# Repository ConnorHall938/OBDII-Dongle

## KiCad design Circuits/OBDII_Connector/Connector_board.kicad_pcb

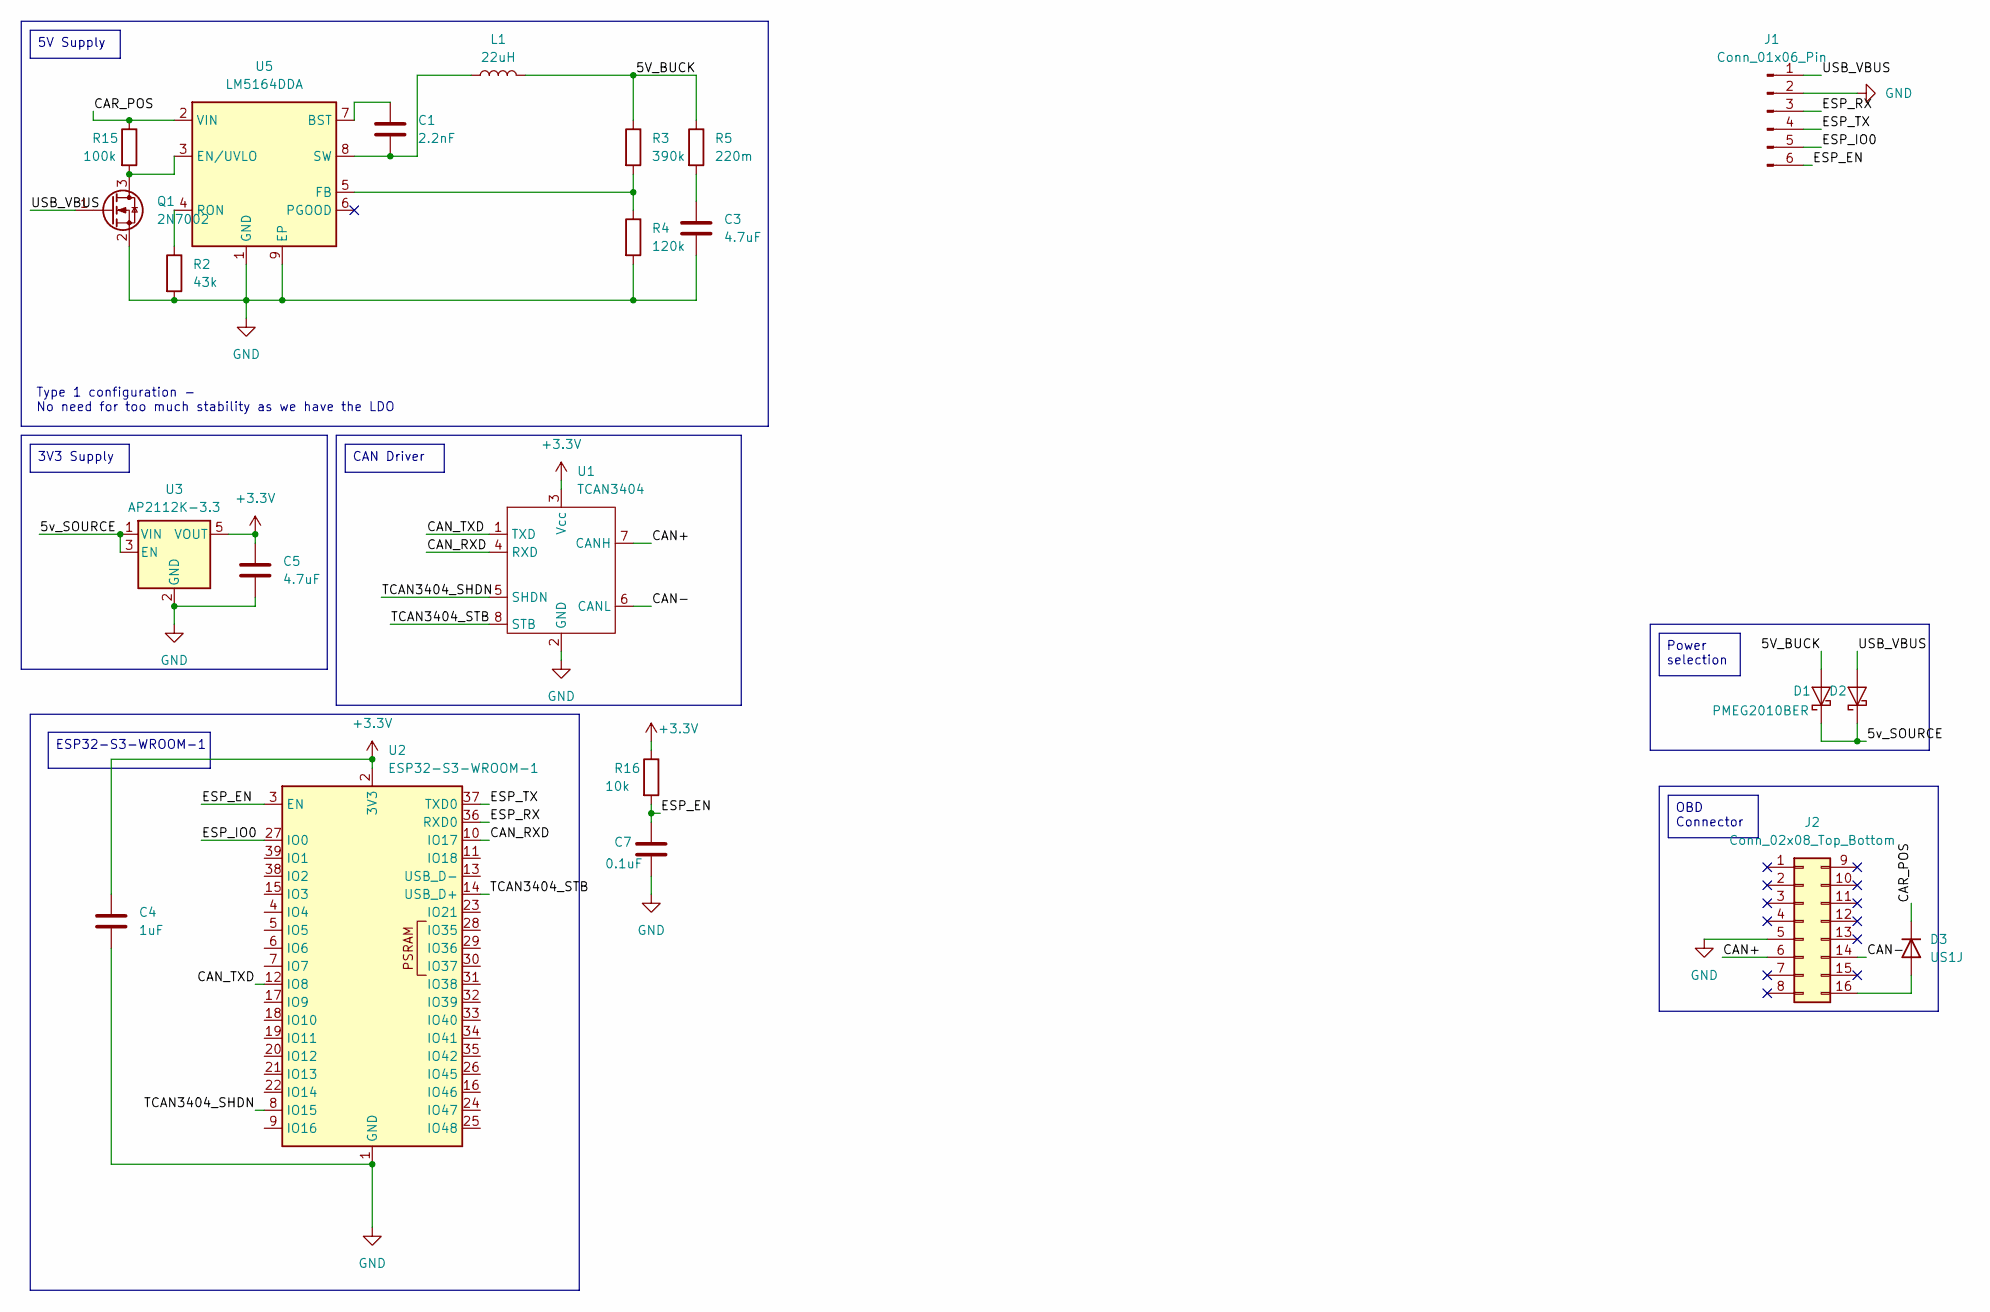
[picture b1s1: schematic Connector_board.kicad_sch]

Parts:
C1: 2.2nF; C_0805_2012Metric_Pad1.18x1.45mm_HandSolder
C3, C5: 4.7uF; C_0805_2012Metric_Pad1.18x1.45mm_HandSolder
C4: 1uF; C_0805_2012Metric_Pad1.18x1.45mm_HandSolder
C7: 0.1uF; C_0805_2012Metric_Pad1.18x1.45mm_HandSolder
D1, D2: PMEG2010BER; Nexperia_CFP3_SOD-123W
D3: US1J; D_SMA
J1: Conn_01x06_Pin; PinSocket_1x06_P2.54mm_Vertical
J2: Conn_02x08_Top_Bottom; PinSocket_2x08_P2.54mm_Vertical
L1: 22uH; L_Bourns_SRN6045TA
Q1: 2N7002; SOT-23
R2: 43k; R_0603_1608Metric_Pad0.98x0.95mm_HandSolder
R3: 390k; R_0603_1608Metric_Pad0.98x0.95mm_HandSolder
R4: 120k; R_0603_1608Metric_Pad0.98x0.95mm_HandSolder
R5: 220m; R_1206_3216Metric_Pad1.30x1.75mm_HandSolder
R15: 100k; R_0603_1608Metric_Pad0.98x0.95mm_HandSolder
R16: 10k; R_0603_1608Metric_Pad0.98x0.95mm_HandSolder
U1: TCAN3404; SOIC-8_3.9x4.9mm_P1.27mm
U2: ESP32-S3-WROOM-1
U3: AP2112K-3.3; SOT-23-5
U5: LM5164DDA; HSOP-8-1EP_3.9x4.9mm_P1.27mm_EP2.41x3.1mm_ThermalVias

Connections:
+3.3V: C4.1, C5.1, R16.1, U1.3 (Vcc), U2.2 (3V3), U3.5 (VOUT)
/5V_BUCK: D1.2 (A), L1.2, R3.1, R5.1
/5v_SOURCE: D1.1 (K), D2.1 (K), U3.1 (VIN), U3.3 (EN)
/CAN+: J2.6, U1.7 (CANH)
/CAN-: J2.14, U1.6 (CANL)
/CAN_RXD: U1.4 (RXD), U2.10 (IO17)
/CAN_TXD: U1.1 (TXD), U2.12 (IO8)
/CAR_POS: D3.1 (K), R15.1, U5.2 (VIN)
/ESP_EN: C7.1, J1.6, R16.2, U2.3 (EN)
/ESP_IO0: J1.5, U2.27 (IO0)
/ESP_RX: J1.3, U2.36 (RXD0)
/ESP_TX: J1.4, U2.37 (TXD0)
/TCAN3404_SHDN: U1.5 (SHDN), U2.8 (IO15)
/TCAN3404_STB: U1.8 (STB), U2.14 (USB_D+)
/USB_VBUS: D2.2 (A), J1.1, Q1.1 (G)
GND: C3.2, C4.2, C5.2, C7.2, J1.2, J2.5, Q1.2 (S), R2.2, R4.2, U1.2 (GND), U2.1 (GND), U2.40 (GND), U2.41 (GND), U3.2 (GND), U5.1 (GND), U5.9 (EP)
unnamed: C3.1, R5.2
unnamed: D3.2 (A), J2.16
unnamed: Q1.3 (D), R15.2, U5.3 (EN/UVLO)
unnamed: C1.1, U5.7 (BST)
unnamed: R3.2, R4.1, U5.5 (FB)
unnamed: R2.1, U5.4 (RON)
unnamed: C1.2, L1.1, U5.8 (SW)

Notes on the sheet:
Type 1 configuration - No need for too much stability as we have the LDO
5V Supply
3V3 Supply
CAN Driver
Power selection
OBD Connector
ESP32-S3-WROOM-1

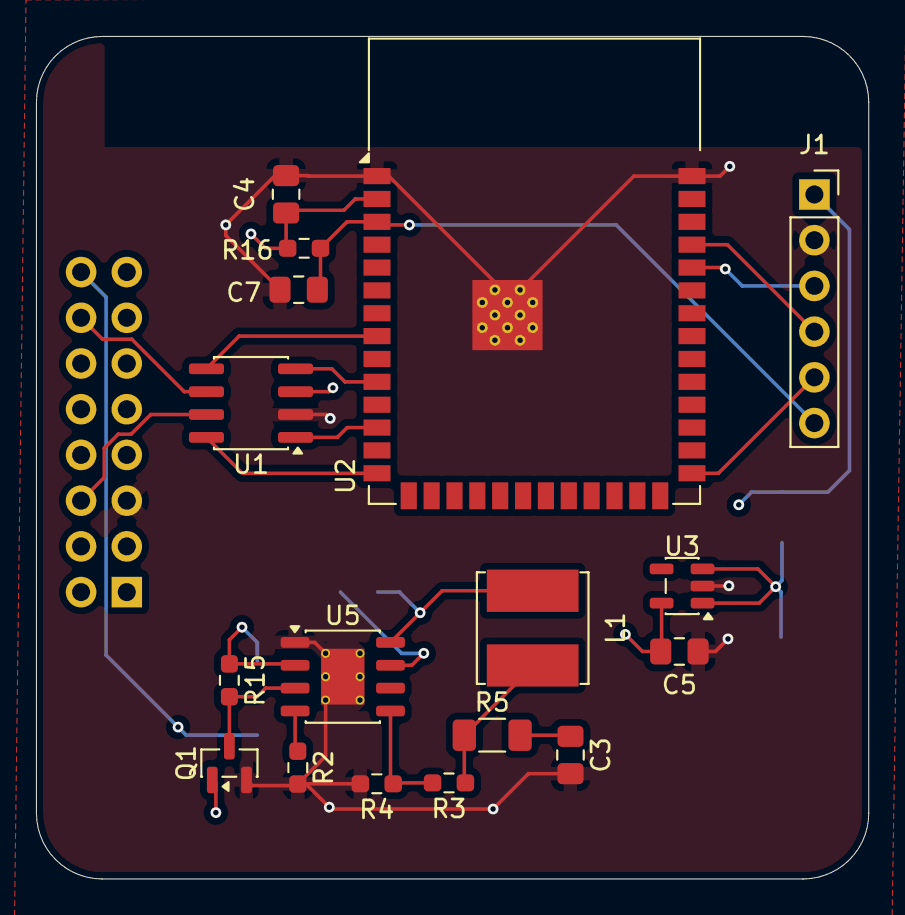
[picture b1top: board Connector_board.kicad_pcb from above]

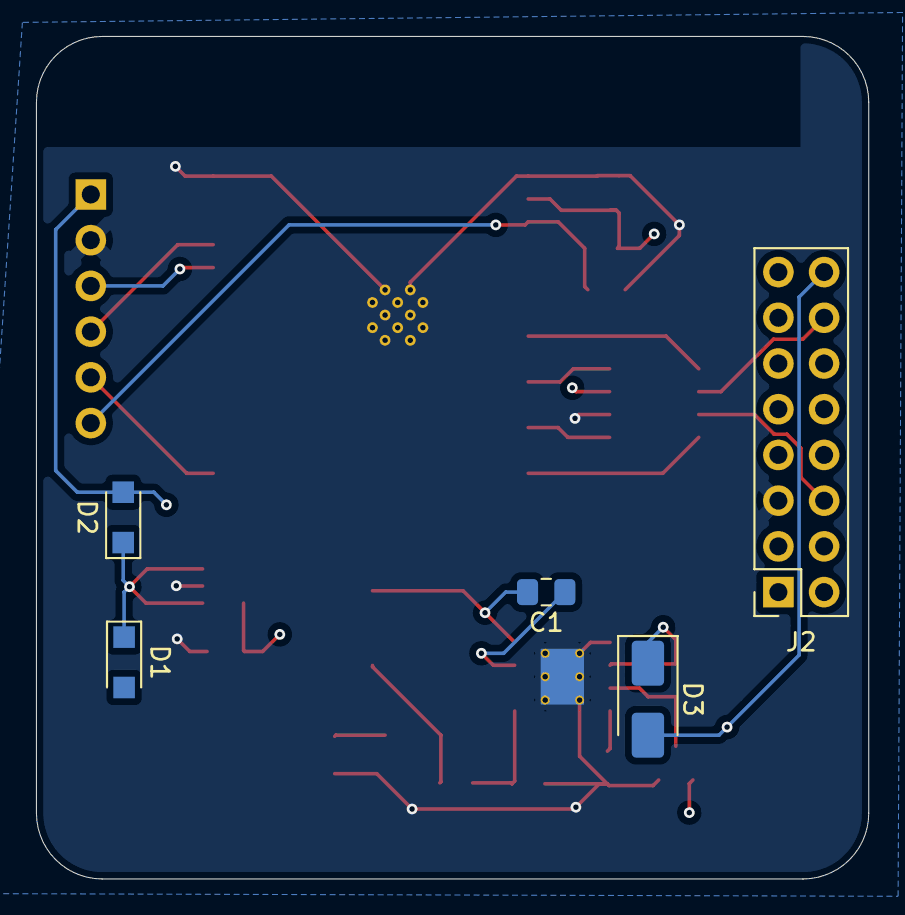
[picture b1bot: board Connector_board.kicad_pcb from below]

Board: 4 copper layers, 46.2 x 46.8 mm, 22 parts (5 on the bottom side), 23 nets.

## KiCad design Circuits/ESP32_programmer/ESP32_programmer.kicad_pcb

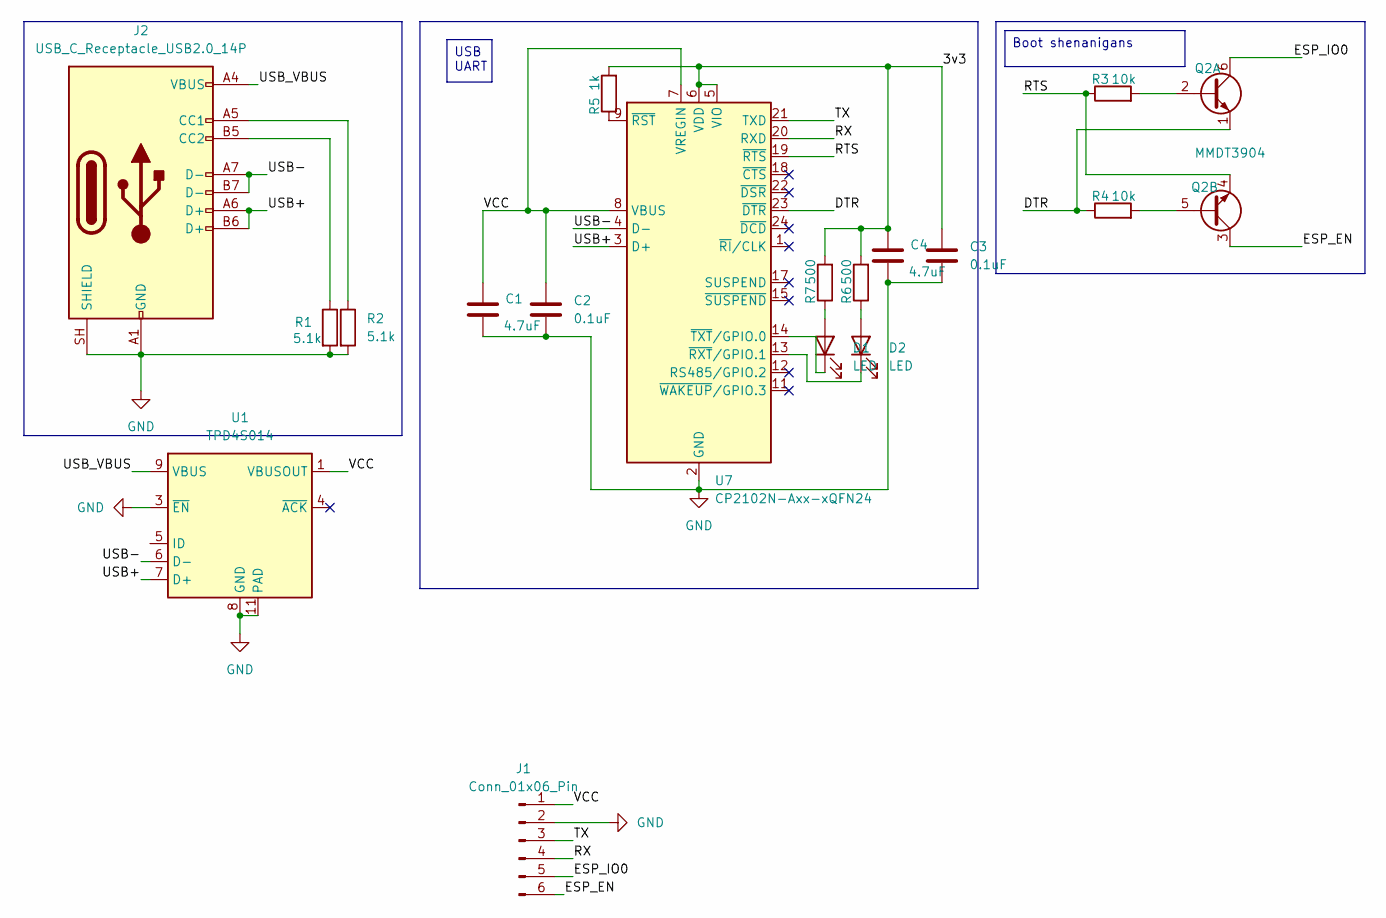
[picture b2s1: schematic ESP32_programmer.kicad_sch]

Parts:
C1, C4: 4.7uF; C_0805_2012Metric_Pad1.18x1.45mm_HandSolder
C2, C3: 0.1uF; C_0805_2012Metric_Pad1.18x1.45mm_HandSolder
D1, D2: LED; LED_1206_3216Metric_Pad1.42x1.75mm_HandSolder
J1: Conn_01x06_Pin; PinSocket_1x06_P2.54mm_Vertical
J2: USB_C_Receptacle_USB2.0_14P; USB_C_Receptacle_Amphenol_12401948E412A
Q2: MMDT3904; SOT-363_SC-70-6
R1, R2: 5.1k; R_0603_1608Metric_Pad0.98x0.95mm_HandSolder
R3, R4: 10k; R_0603_1608Metric_Pad0.98x0.95mm_HandSolder
R5: 1k; R_0603_1608Metric_Pad0.98x0.95mm_HandSolder
R6, R7: 500; R_0603_1608Metric_Pad0.98x0.95mm_HandSolder
U1: TPD4S014; Texas_S-PWSON-N10_ThermalVias
U7: CP2102N-Axx-xQFN24; QFN-24-1EP_4x4mm_P0.5mm_EP2.6x2.6mm

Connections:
/3v3: C3.1, C4.1, R5.2, R6.2, R7.2, U7.5 (VIO), U7.6 (VDD)
/DTR: Q2.1 (E1), R4.1, U7.23 (~DTR)
/ESP_EN: J1.6, Q2.3 (C2)
/ESP_IO0: J1.5, Q2.6 (C1)
/RTS: Q2.4 (E2), R3.1, U7.19 (~RTS)
/RX: J1.4, U7.20 (RXD)
/TX: J1.3, U7.21 (TXD)
/USB+: J2.A6 (D+), J2.B6 (D+), U1.7 (D+), U7.3 (D+)
/USB-: J2.A7 (D-), J2.B7 (D-), U1.6 (D-), U7.4 (D-)
/USB_VBUS: J2.A4 (VBUS), J2.A9 (VBUS), J2.B4 (VBUS), J2.B9 (VBUS), U1.9 (VBUS), U1.10 (VBUS)
/VCC: C1.1, C2.1, J1.1, U1.1 (VBUSOUT), U1.2 (VBUSOUT), U7.7 (VREGIN), U7.8 (VBUS)
GND: C1.2, C2.2, C3.2, C4.2, J1.2, J2.A1 (GND), J2.A12 (GND), J2.B1 (GND), J2.B12 (GND), J2.SH (SHIELD), R1.2, R2.2, U1.3 (~EN), U1.8 (GND), U1.11 (PAD), U7.2 (GND), U7.25 (GND)
unnamed: D1.2 (A), R7.1
unnamed: D1.1 (K), U7.14 (~TXT/GPIO.0)
unnamed: D2.2 (A), R6.1
unnamed: D2.1 (K), U7.13 (~RXT/GPIO.1)
unnamed: J2.A5 (CC1), R2.1
unnamed: J2.B5 (CC2), R1.1
unnamed: Q2.2 (B1), R3.2
unnamed: Q2.5 (B2), R4.2
unnamed: R5.1, U7.9 (~RST)

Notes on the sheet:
USB UART
Boot shenanigans

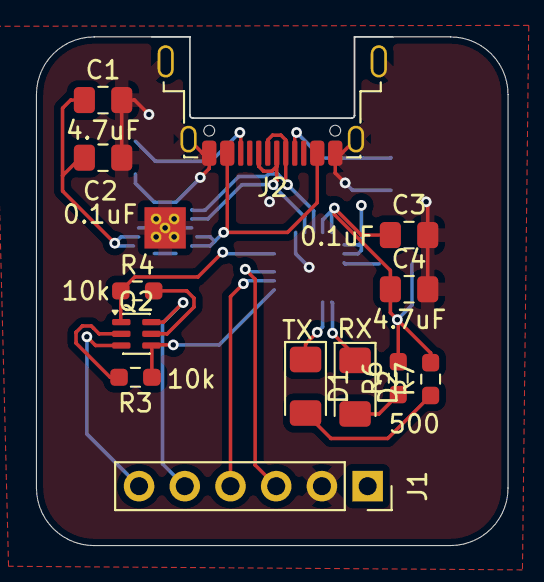
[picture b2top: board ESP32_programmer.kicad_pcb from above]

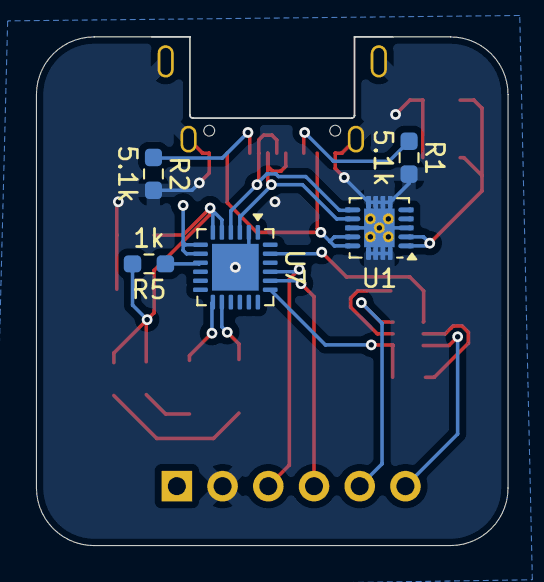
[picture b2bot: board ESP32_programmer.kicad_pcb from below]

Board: 4 copper layers, 26.2 x 28.3 mm, 18 parts (5 on the bottom side), 21 nets.

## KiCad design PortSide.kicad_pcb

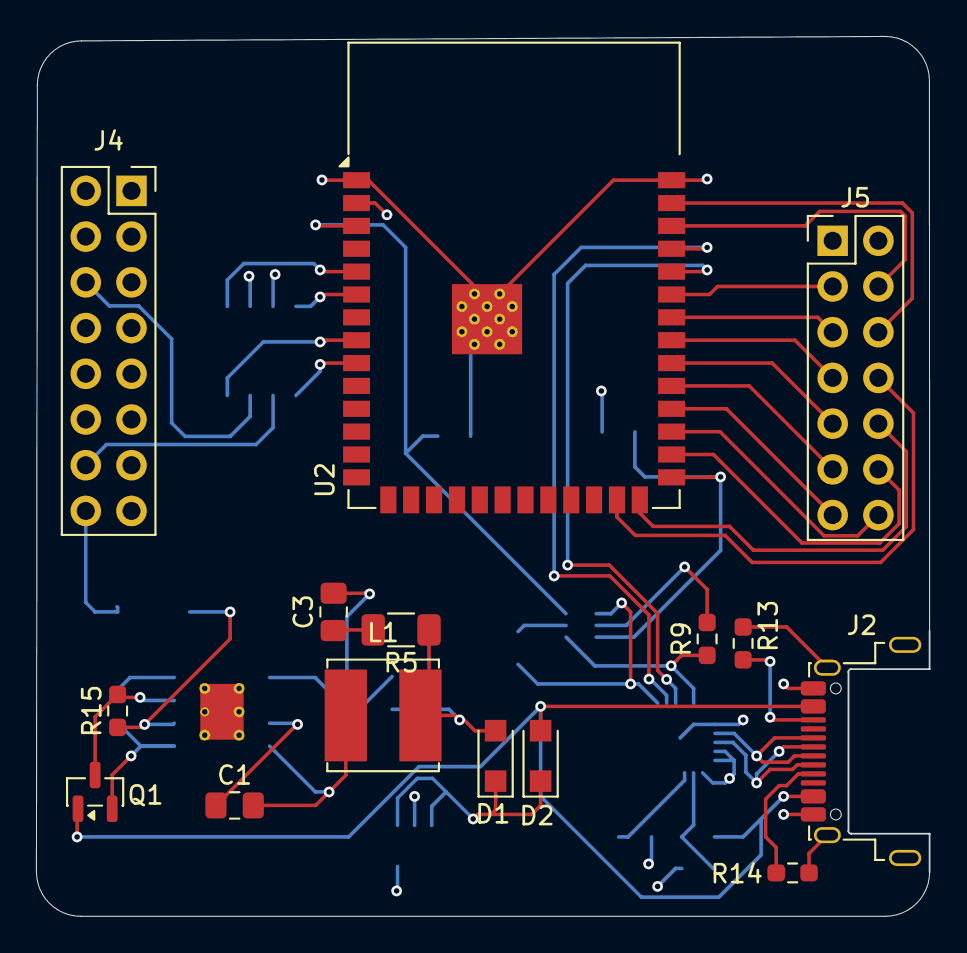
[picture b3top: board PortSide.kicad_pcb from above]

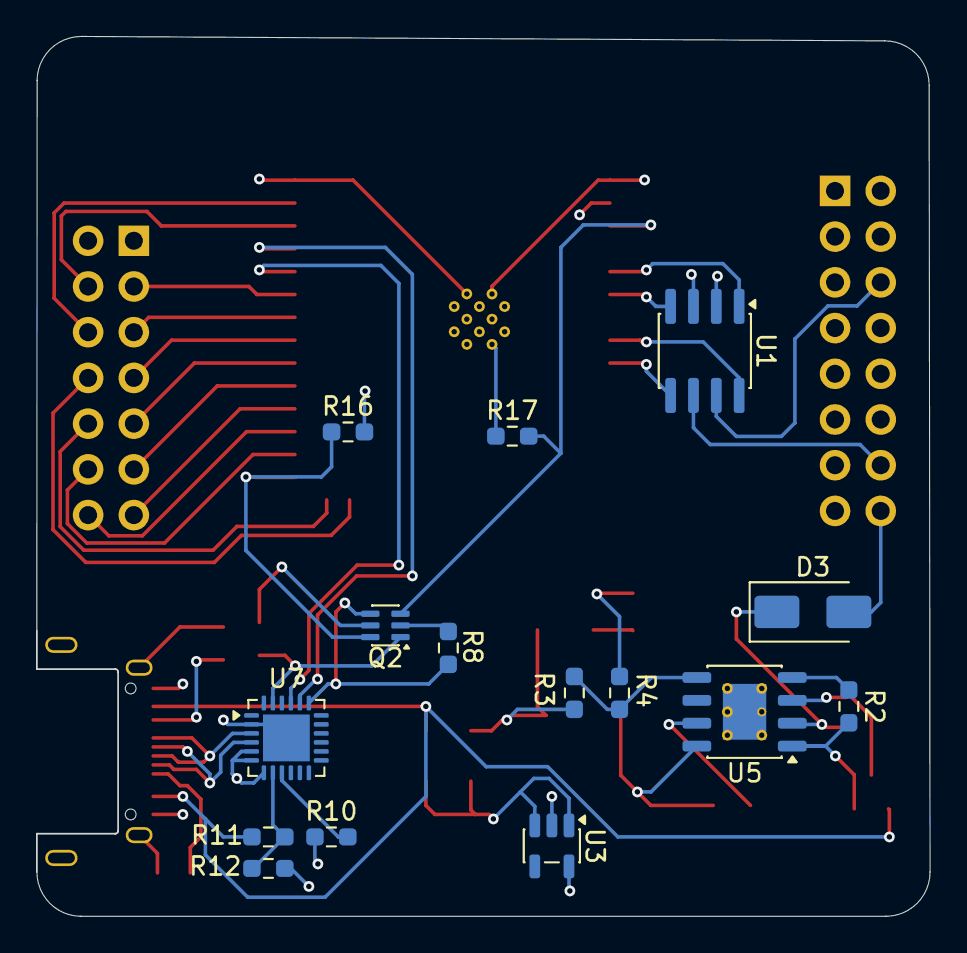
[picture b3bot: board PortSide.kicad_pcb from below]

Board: 4 copper layers, 49.6 x 48.9 mm, 30 parts (15 on the bottom side), 45 nets.

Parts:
C1: 2.2nF; C_0805_2012Metric_Pad1.18x1.45mm_HandSolder
C3: 4.7uF; C_0805_2012Metric_Pad1.18x1.45mm_HandSolder
D1, D2: PMEG2010BER; Nexperia_CFP3_SOD-123W
D3: US1J; D_SMA
J2: USB_C_Receptacle_USB2.0_14P; USB_C_Receptacle_Amphenol_12401948E412A
J4: Conn_02x08_Top_Bottom; PinSocket_2x08_P2.54mm_Vertical
J5: Conn_02x07_Counter_Clockwise; PinHeader_2x07_P2.54mm_Vertical
L1: 22uH; L_Bourns_SRN6045TA
Q1: 2N7002; SOT-23
Q2: MMDT3904; SOT-363_SC-70-6
R2: 43k; R_0603_1608Metric_Pad0.98x0.95mm_HandSolder
R3: 390k; R_0603_1608Metric_Pad0.98x0.95mm_HandSolder
R4: 120k; R_0603_1608Metric_Pad0.98x0.95mm_HandSolder
R5: 220m; R_1206_3216Metric_Pad1.30x1.75mm_HandSolder
R8, R9, R10: 1k; R_0603_1608Metric_Pad0.98x0.95mm_HandSolder
R11: 22k; R_0603_1608Metric_Pad0.98x0.95mm_HandSolder
R12: 47k; R_0603_1608Metric_Pad0.98x0.95mm_HandSolder
R13, R14: 5.1k; R_0603_1608Metric_Pad0.98x0.95mm_HandSolder
R15: 100k; R_0603_1608Metric_Pad0.98x0.95mm_HandSolder
R16, R17: 10k; R_0603_1608Metric_Pad0.98x0.95mm_HandSolder
U1: TCAN3404; SOIC-8_3.9x4.9mm_P1.27mm
U2: ESP32-S3-WROOM-1
U3: AP2112K-3.3; SOT-23-5
U5: LM5164DDA; HSOP-8-1EP_3.9x4.9mm_P1.27mm_EP2.41x3.1mm_ThermalVias
U7: CP2102N-Axx-xQFN24; QFN-24-1EP_4x4mm_P0.5mm_EP2.6x2.6mm

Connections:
+3.3V: J5.1, R10.1, U1.3 (Vcc), U2.2 (3V3), U3.5 (VOUT), U7.5 (VIO), U7.6 (VDD), U7.7 (VREGIN)
/5V_BUCK: D1.2 (A), L1.2, R3.1, R5.1
/5v_SOURCE: D1.1 (K), D2.1 (K), U3.1 (VIN), U3.3 (EN)
/CANH: J4.6, U1.7 (CANH)
/CANL: J4.14, U1.6 (CANL)
/CAN_RXD: U1.4 (RXD), U2.6 (IO6)
/CAN_TXD: U1.1 (TXD), U2.5 (IO5)
/CAR_POS: D3.1 (K), R15.1, U5.2 (VIN)
/DTR: Q2.1 (E1), R9.1, U7.23 (~DTR)
/ESP_EN: Q2.3 (C2), R17.2, U2.3 (EN)
/ESP_IO0: Q2.6 (C1), R16.1, U2.27 (IO0)
/ESP_RX: U2.36 (RXD0), U7.21 (TXD)
/ESP_TX: U2.37 (TXD0), U7.20 (RXD)
/LCD_CS: J5.3, U2.35 (IO42)
/LCD_DC: J5.5, U2.34 (IO41)
/LCD_LED: J5.8, U2.25 (IO48)
/LCD_MISO: J5.9, U2.32 (IO39)
/LCD_MOSI: J5.6, U2.39 (IO1)
/LCD_RESET: J5.4, U2.38 (IO2)
/LCD_SCK: J5.7, U2.33 (IO40)
/LCD_T_CLK: J5.10, U2.26 (IO45)
/LCD_T_CS: J5.11, U2.31 (IO38)
/LCD_T_DIN: J5.12, U2.28 (IO35)
/LCD_T_DO: J5.13, U2.30 (IO37)
/LCD_T_IRQ: J5.14, U2.29 (IO36)
/RTS: Q2.4 (E2), R8.1, U7.19 (~RTS)
/TCAN3404_SHDN: U1.5 (SHDN), U2.9 (IO16)
/TCAN3404_STB: U1.8 (STB), U2.8 (IO15)
/USB+: J2.A6 (D+), J2.B6 (D+), U7.3 (D+)
/USB-: J2.A7 (D-), J2.B7 (D-), U7.4 (D-)
/USB_VBUS: D2.2 (A), J2.A4 (VBUS), J2.A9 (VBUS), J2.B4 (VBUS), J2.B9 (VBUS), Q1.1 (G), R11.1
GND: C3.2, J2.A1 (GND), J2.A12 (GND), J2.B1 (GND), J2.B12 (GND), J2.SH (SHIELD), J4.5, J5.2, Q1.2 (S), R2.2, R4.2, R12.2, R13.2, R14.2, R16.2, R17.1, U1.2 (GND), U2.1 (GND), U2.40 (GND), U2.41 (GND), U3.2 (GND), U5.1 (GND), U5.9 (EP), U7.2 (GND), U7.25 (GND)
unnamed: C3.1, R5.2
unnamed: D3.2 (A), J4.16
unnamed: J2.A5 (CC1), R14.1
unnamed: J2.B5 (CC2), R13.1
unnamed: Q1.3 (D), R15.2, U5.3 (EN/UVLO)
unnamed: Q2.2 (B1), R8.2
unnamed: Q2.5 (B2), R9.2
unnamed: C1.1, U5.7 (BST)
unnamed: R3.2, R4.1, U5.5 (FB)
unnamed: R2.1, U5.4 (RON)
unnamed: C1.2, L1.1, U5.8 (SW)
unnamed: R11.2, R12.1, U7.8 (VBUS)
unnamed: R10.2, U7.9 (~RST)
